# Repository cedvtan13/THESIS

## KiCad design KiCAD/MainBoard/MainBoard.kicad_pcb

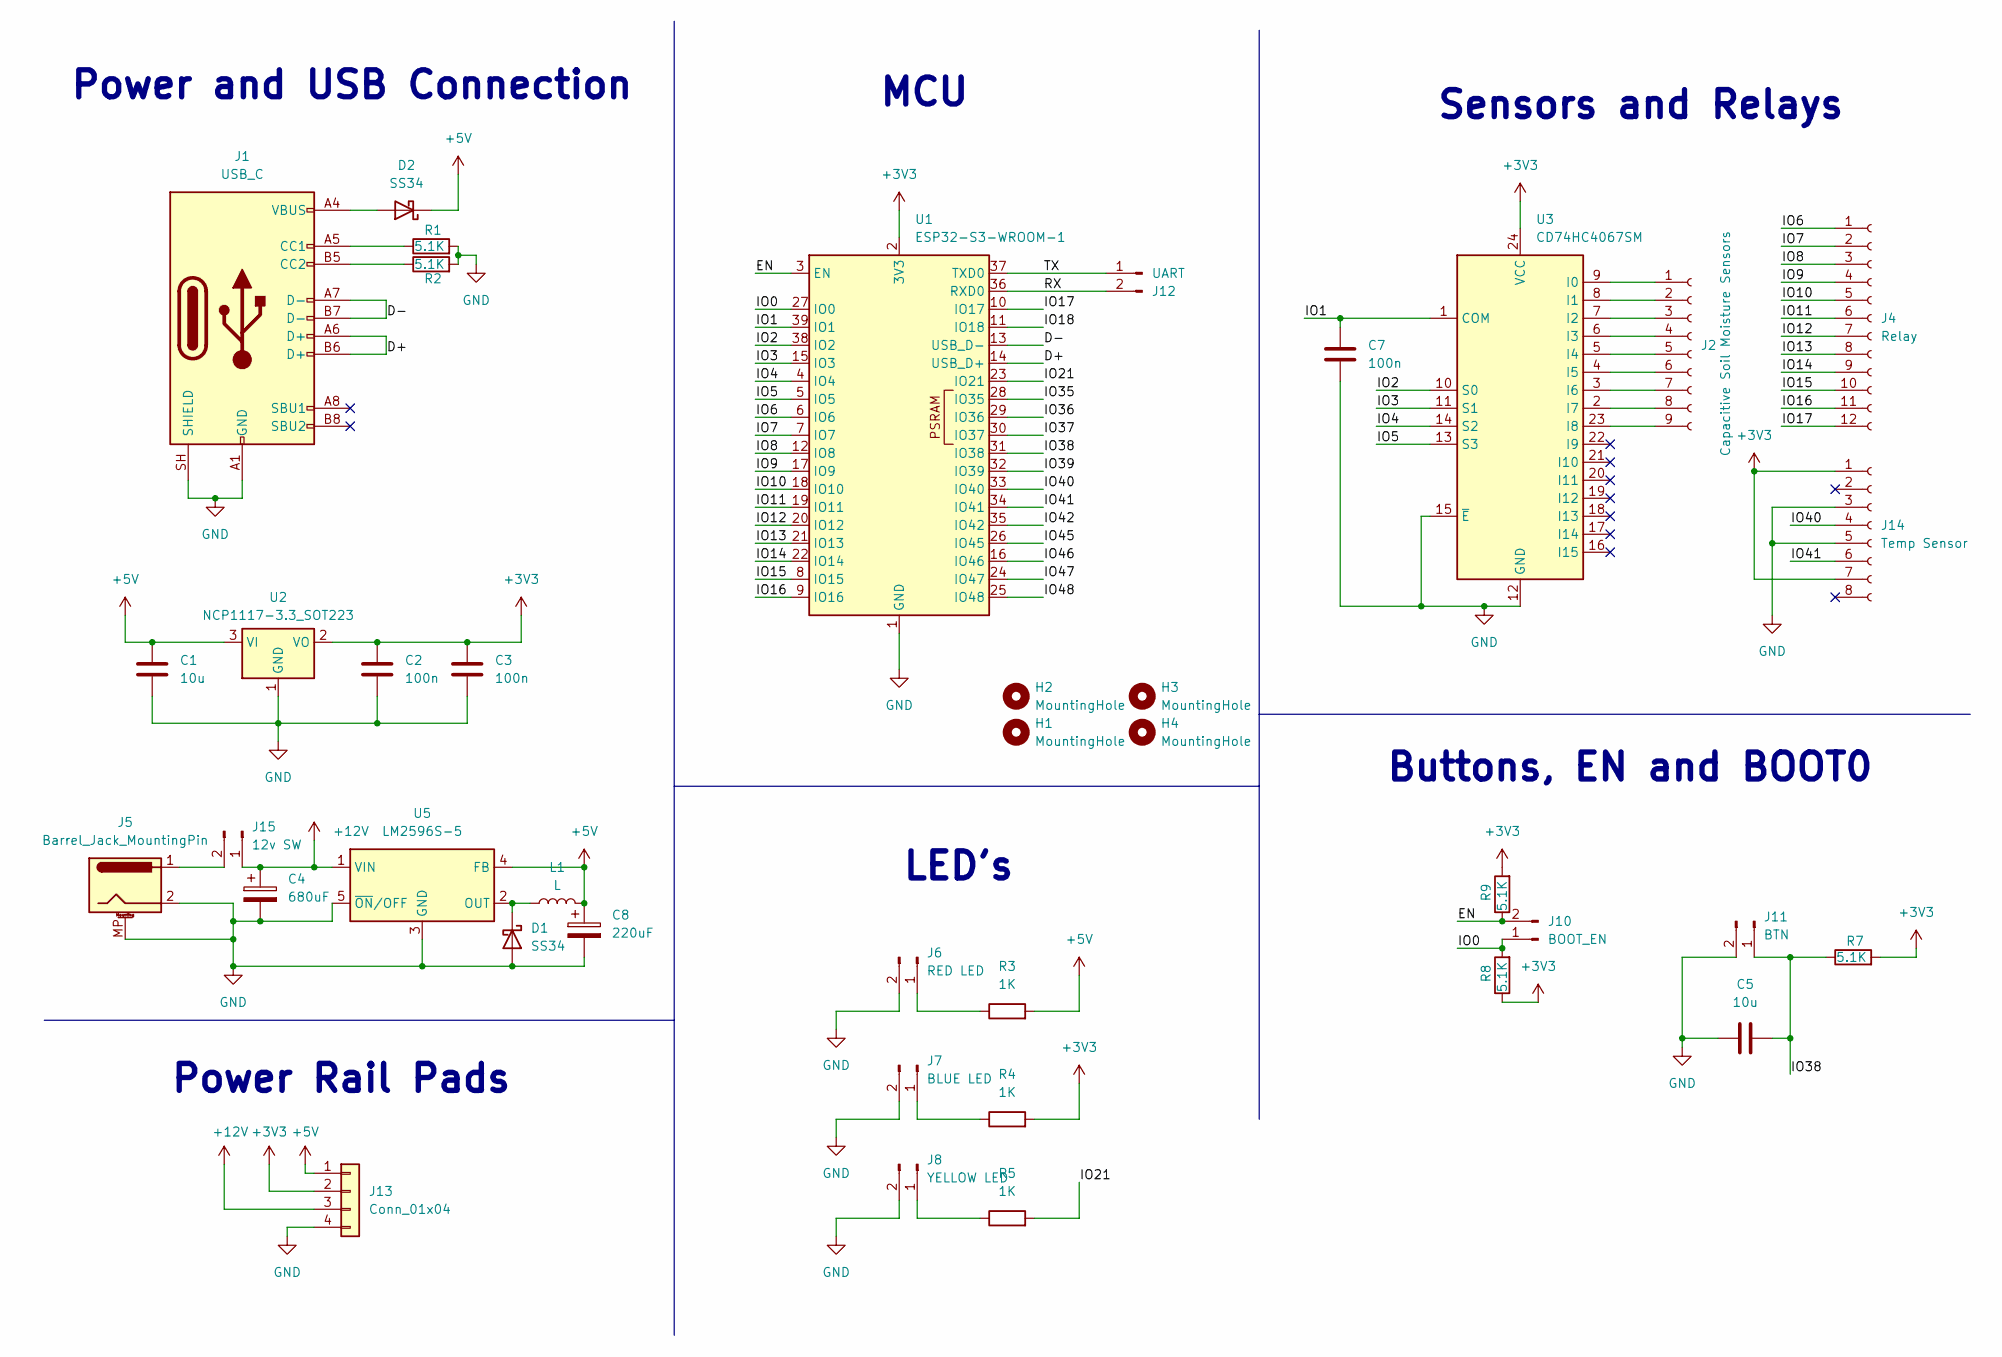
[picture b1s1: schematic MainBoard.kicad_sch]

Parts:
C1, C5: 10u; C_0805_2012Metric_Pad1.18x1.45mm_HandSolder
C2, C3, C7: 100n; C_0805_2012Metric_Pad1.18x1.45mm_HandSolder
C4: 680uF; CP_Elec_8x10.5
C8: 220uF; CP_Elec_8x10.5
D1, D2: SS34; D_SMA
H1, H2, H3, H4: MountingHole; MountingHole_2.2mm_M2
J1: USB_C; USB_C_Receptacle_HRO_TYPE-C-31-M-12
J2: Capacitive Soil Moisture Sensors; PinSocket_1x09_P2.54mm_Vertical
J4: Relay; PinSocket_1x12_P2.54mm_Vertical
J5: Barrel_Jack_MountingPin; BarrelJack_GCT_DCJ200-10-A_Horizontal
J6: RED LED; JST_XH_B2B-XH-A_1x02_P2.50mm_Vertical
J7: BLUE LED; JST_XH_B2B-XH-A_1x02_P2.50mm_Vertical
J8: YELLOW LED; JST_XH_B2B-XH-A_1x02_P2.50mm_Vertical
J10: BOOT_EN; JST_XH_B2B-XH-A_1x02_P2.50mm_Vertical
J11: BTN; JST_XH_B2B-XH-A_1x02_P2.50mm_Vertical
J12: UART; JST_XH_B2B-XH-A_1x02_P2.50mm_Vertical
J13: Conn_01x04; SolderWire-0.75sqmm_1x04_P4.8mm_D1.25mm_OD2.3mm
J14: Temp Sensor; PinHeader_1x08_P2.54mm_Vertical
J15: 12v SW; JST_XH_B2B-XH-A_1x02_P2.50mm_Vertical
L1: L; L_12x12mm_H8mm
R1, R2, R7, R8, R9: 5.1K; R_0603_1608Metric
R3, R4, R5: 1K; R_0805_2012Metric_Pad1.20x1.40mm_HandSolder
U1: ESP32-S3-WROOM-1
U2: NCP1117-3.3_SOT223; SOT-223-3_TabPin2
U3: CD74HC4067SM; SSOP-24_5.3x8.2mm_P0.65mm
U5: LM2596S-5; TO-263-5_TabPin3

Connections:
+3V3: C2.1, C3.1, J13.2, J14.1, J14.7, R4.2, R7.2, R8.1, R9.2, U1.2 (3V3), U2.2 (VO), U3.24 (VCC)
+5V: C1.1, C8.1, D2.1 (K), J13.1, L1.2, R3.2, U2.3 (VI), U5.4 (FB)
+12V: C4.1, J13.3, J15.1, U5.1 (VIN)
/D+: J1.A6 (D+), J1.B6 (D+), U1.14 (USB_D+)
/D-: J1.A7 (D-), J1.B7 (D-), U1.13 (USB_D-)
/EN: J10.2, R9.1, U1.3 (EN)
/IO0: J10.1, R8.2, U1.27 (IO0)
/IO1: C7.1, U1.39 (IO1), U3.1 (COM)
/IO2: U1.38 (IO2), U3.10 (S0)
/IO3: U1.15 (IO3), U3.11 (S1)
/IO4: U1.4 (IO4), U3.14 (S2)
/IO5: U1.5 (IO5), U3.13 (S3)
/IO6: J4.1, U1.6 (IO6)
/IO7: J4.2, U1.7 (IO7)
/IO8: J4.3, U1.12 (IO8)
/IO9: J4.4, U1.17 (IO9)
/IO10: J4.5, U1.18 (IO10)
/IO11: J4.6, U1.19 (IO11)
/IO12: J4.7, U1.20 (IO12)
/IO13: J4.8, U1.21 (IO13)
/IO14: J4.9, U1.22 (IO14)
/IO15: J4.10, U1.8 (IO15)
/IO16: J4.11, U1.9 (IO16)
/IO17: J4.12, U1.10 (IO17)
/IO18: U1.11 (IO18)
/IO21: R5.2, U1.23 (IO21)
/IO35: U1.28 (IO35)
/IO36: U1.29 (IO36)
/IO37: U1.30 (IO37)
/IO38: C5.2, J11.1, R7.1, U1.31 (IO38)
/IO39: U1.32 (IO39)
/IO40: J14.4, U1.33 (IO40)
/IO41: J14.6, U1.34 (IO41)
/IO42: U1.35 (IO42)
/IO45: U1.26 (IO45)
/IO46: U1.16 (IO46)
/IO47: U1.24 (IO47)
/IO48: U1.25 (IO48)
/RX: J12.2, U1.36 (RXD0)
/TX: J12.1, U1.37 (TXD0)
GND: C1.2, C2.2, C3.2, C4.2, C5.1, C7.2, C8.2, D1.2 (A), J1.A1 (GND), J1.A12 (GND), J1.B1 (GND), J1.B12 (GND), J1.SH (SHIELD), J5.2, J5.MP (MountPin), J6.2, J7.2, J8.2, J11.2, J13.4, J14.3, J14.5, R1.2, R2.2, U1.1 (GND), U1.40 (GND), U1.41 (GND), U2.1 (GND), U3.12 (GND), U3.15 (~E), U5.3 (GND), U5.5 (~ON/OFF)
unnamed: D1.1 (K), L1.1, U5.2 (OUT)
unnamed: D2.2 (A), J1.A4 (VBUS), J1.A9 (VBUS), J1.B4 (VBUS), J1.B9 (VBUS)
unnamed: J1.A5 (CC1), R1.1
unnamed: J1.B5 (CC2), R2.1
unnamed: J2.1, U3.9 (I0)
unnamed: J2.2, U3.8 (I1)
unnamed: J2.3, U3.7 (I2)
unnamed: J2.4, U3.6 (I3)
unnamed: J2.5, U3.5 (I4)
unnamed: J2.6, U3.4 (I5)
unnamed: J2.7, U3.3 (I6)
unnamed: J2.8, U3.2 (I7)
unnamed: J2.9, U3.23 (I8)
unnamed: J6.1, R3.1
unnamed: J7.1, R4.1
unnamed: J8.1, R5.1
unnamed: J5.1, J15.2

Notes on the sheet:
Buttons, EN and BOOT0
MCU
LED's
Power and USB Connection
Power Rail Pads
Sensors and Relays

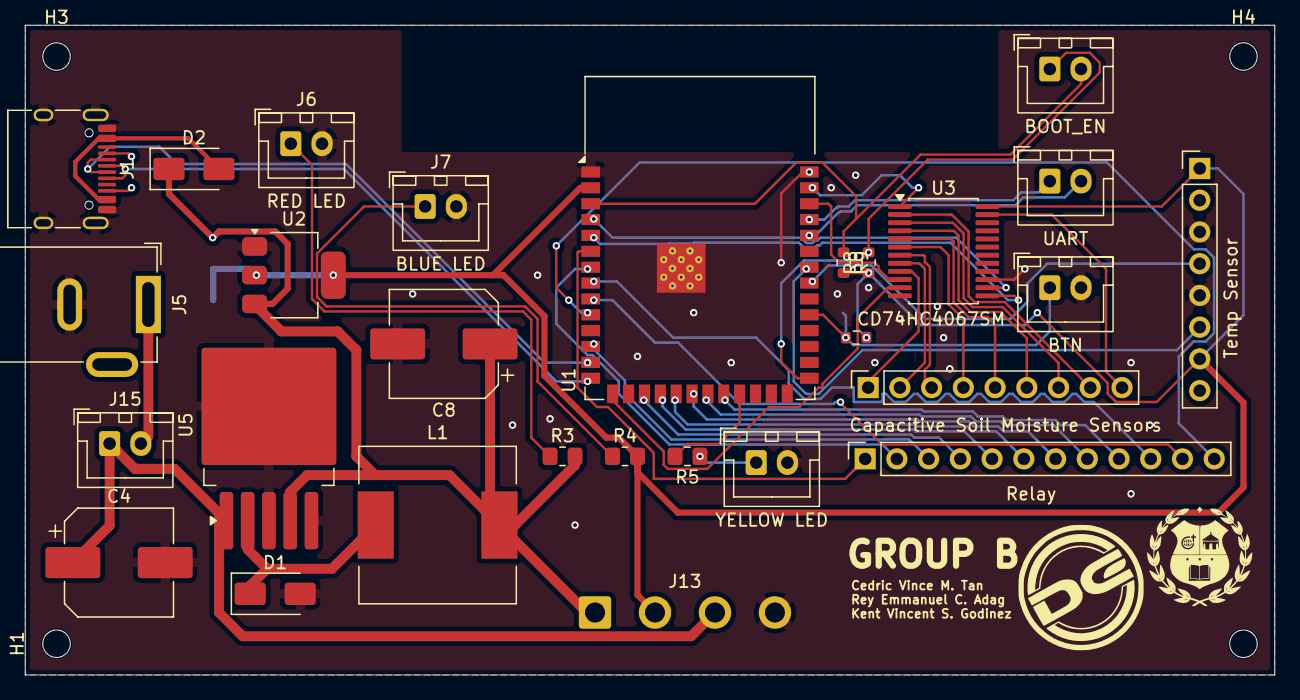
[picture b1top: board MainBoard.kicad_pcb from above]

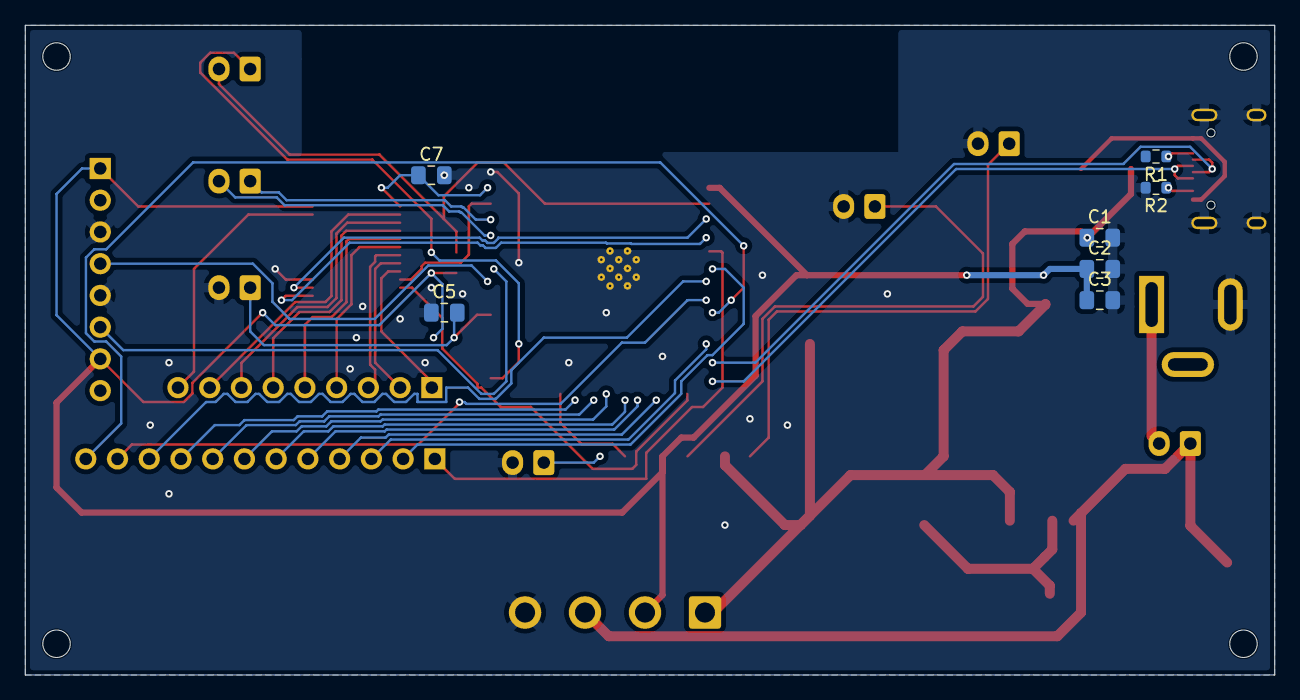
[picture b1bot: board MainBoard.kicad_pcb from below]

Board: 2 copper layers, 100.0 x 52.0 mm, 39 parts (7 on the bottom side), 48 nets.
